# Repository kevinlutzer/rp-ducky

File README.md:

# RP Ducky

A RP2040 based keystroke injector that uses standard [Ducky Script](https://docs.hak5.org/hak5-usb-rubber-ducky/duckyscript-tm-quick-reference). Unlike the original Rubber Ducky from Hak5, this module does not require the scripts to be loaded over an SD card. Instead, you can start the RP Ducky in USB Storage mode to both update the code and the scripts on the device.

## Fabrication

The PCBs are fabricated as a 4 layer board with JLCPCBs JLC04161H-7628A stackup. The bill of materials and the gerber files are available in the [fab](./fab) folder. The USB covering the PCB is designed for can be found on [Alibaba](https://www.alibaba.com/product-detail/Custom-Logo-2-0-3-0_1600456187162.html?spm=a2700.galleryofferlist.p_offer.d_image.72eb3e85w6j8S4&s=p) or on [Amazon](https://www.amazon.ca/RAOYI-Drives-Memory-Storage-Swivel/dp/B07KS1TTCH?ref_=ast_slp_dp&th=1) 

## Usage

To upload the code and scripts to the RP Ducky, you need to put the RP Ducky into USB Storage mode. To do this, hold the button `BOOT` and `RESET` buttons down while plugging the device into a computer. Release the `BOOT` button first and then the `RESET` button. The device will show up as storage device. Copy Adafruit's [Raspberry Pi Pico UF2 Circuit Python file](https://circuitpython.org/board/raspberry_pi_pico/) on to the RP Ducky. You can then copy the contents of [code](./code/) onto the device. To run the test script, copy `sample/payloads/rickroll_macos.txt` to the RP Ducky's root directory and rename it to `payload.txt`

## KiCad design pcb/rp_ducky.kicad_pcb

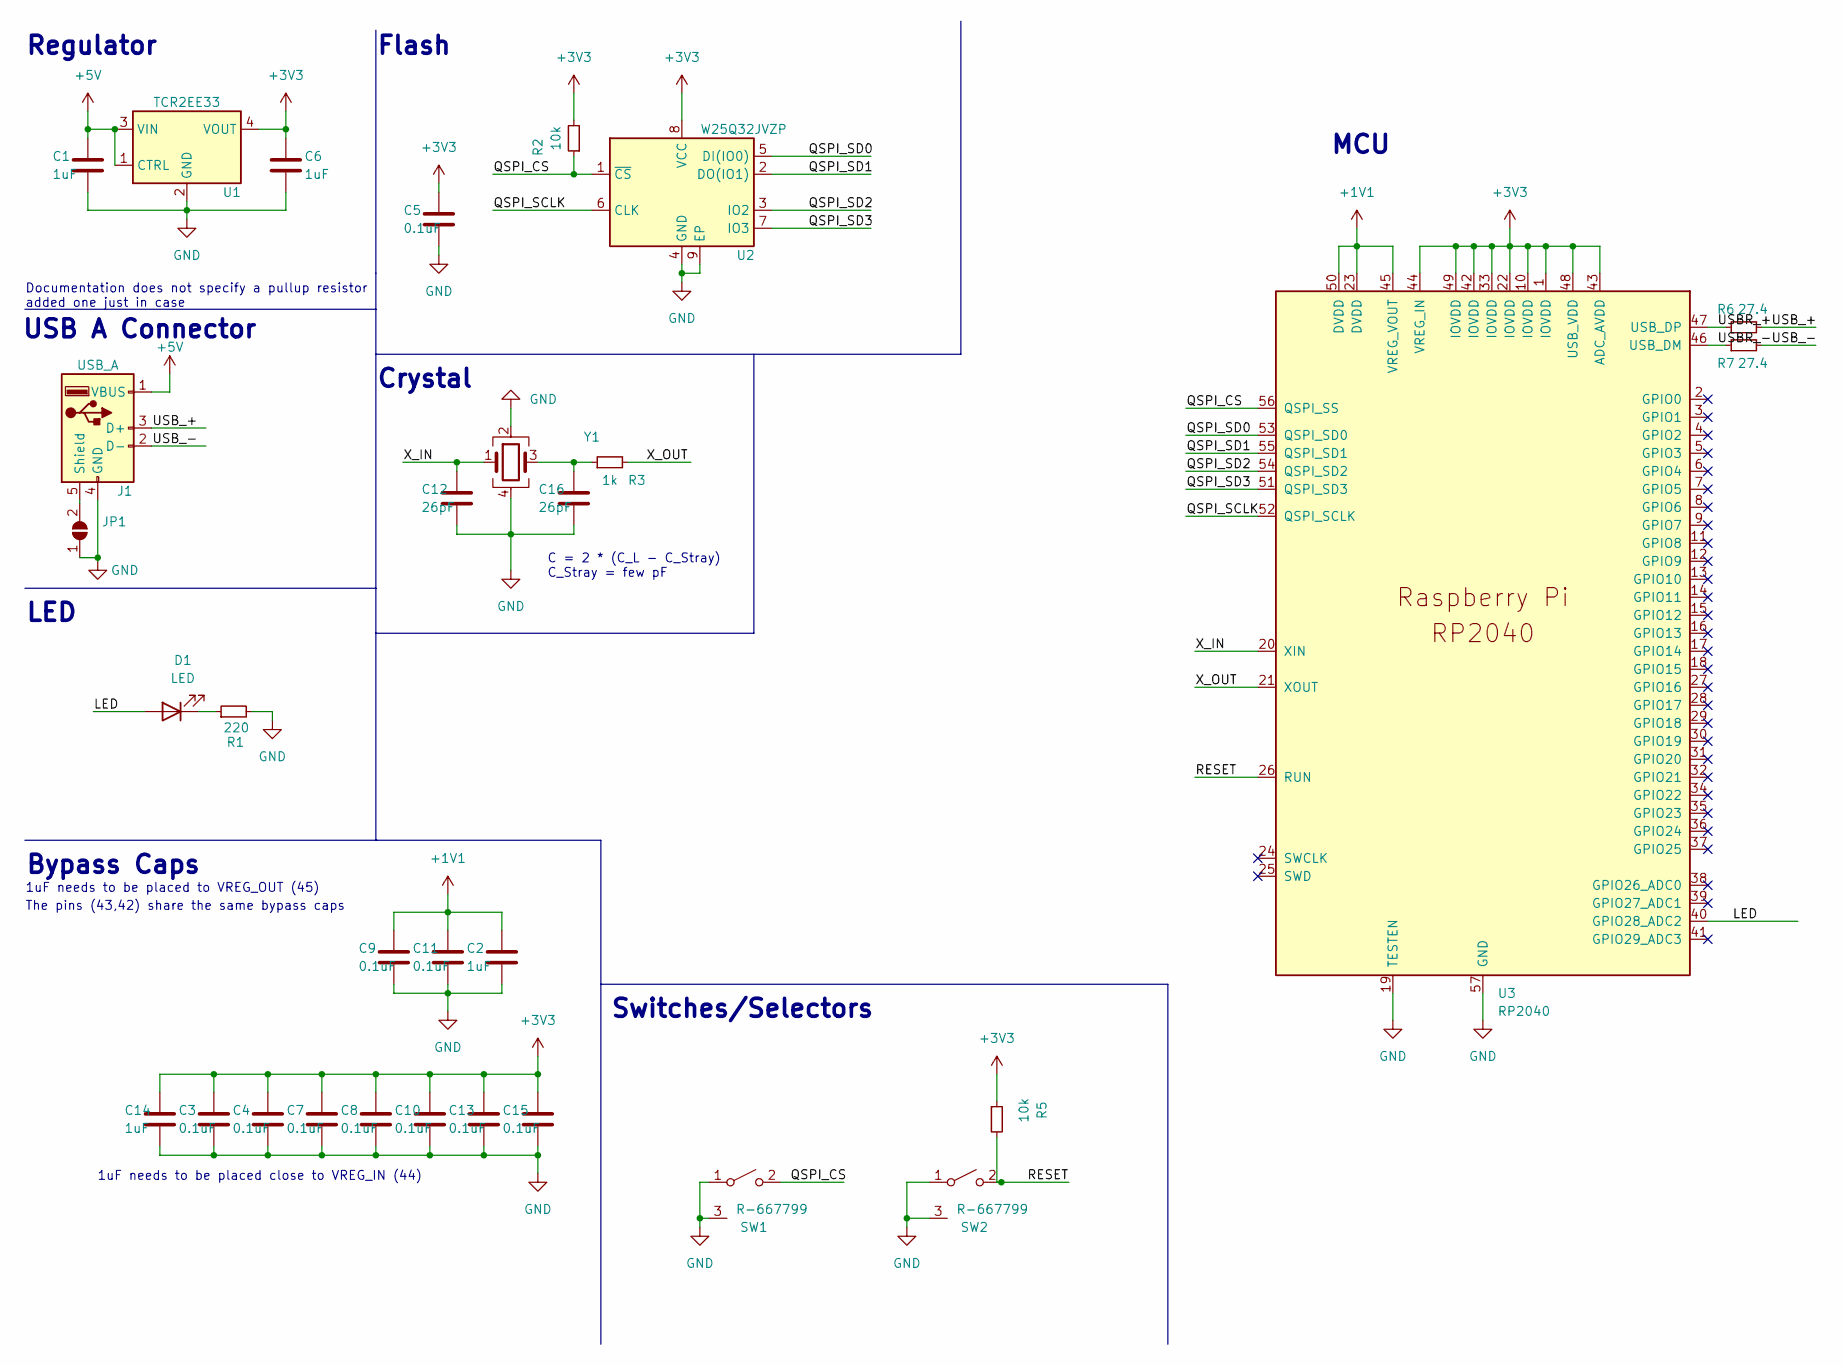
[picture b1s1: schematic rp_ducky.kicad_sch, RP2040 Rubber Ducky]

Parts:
C1, C2, C6: 1uF; C_0402_1005Metric_Pad0.74x0.62mm_HandSolder
C3, C4, C5, C13: 0.1uF; C_0402_1005Metric
C7, C8, C9, C10, C11, C15: 0.1uF; C_0402_1005Metric_Pad0.74x0.62mm_HandSolder
C12, C16: 26pF; C_0402_1005Metric
C14: 1uF; C_0402_1005Metric
D1: LED; LED_0603_1608Metric
J1: USB_A; USB3_A_Plug_Wuerth_629004113921_Horizontal
JP1: SolderJumper_2_Open; SolderJumper-2_P1.3mm_Open_TrianglePad1.0x1.5mm
R1: 220; R_0402_1005Metric
R2, R5: 10k; R_0402_1005Metric
R3: 1k; R_0402_1005Metric
R6, R7: 27.4; R_0402_1005Metric
SW1, SW2: R-667799
U1: TCR2EE33; SOT-553
U2: W25Q32JVZP; WSON-8-1EP_6x5mm_P1.27mm_EP3.4x4.3mm
U3: RP2040; RP2040-QFN-56
Y1: Crystal_GND24; Crystal_SMD_2520-4Pin_2.5x2.0mm

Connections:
+1V1: C2.2, C9.2, C11.2, U3.23 (DVDD), U3.45 (VREG_VOUT), U3.50 (DVDD)
+3V3: C3.2, C4.2, C5.2, C6.2, C7.2, C8.2, C10.2, C13.2, C14.2, C15.2, R2.2, R5.1, U1.4 (VOUT), U2.8 (VCC), U3.1 (IOVDD), U3.10 (IOVDD), U3.22 (IOVDD), U3.33 (IOVDD), U3.42 (IOVDD), U3.43 (ADC_AVDD), U3.44 (VREG_IN), U3.48 (USB_VDD), U3.49 (IOVDD)
+5V: C1.2, J1.1 (VBUS), U1.1 (CTRL), U1.3 (VIN)
/LED: D1.2 (A), U3.40 (GPIO28_ADC2)
/QSPI_CS: R2.1, SW1.2 (B), U2.1 (~CS), U3.56 (QSPI_SS)
/QSPI_SCLK: U2.6 (CLK), U3.52 (QSPI_SCLK)
/QSPI_SD0: U2.5 (DI(IO0)), U3.53 (QSPI_SD0)
/QSPI_SD1: U2.2 (DO(IO1)), U3.55 (QSPI_SD1)
/QSPI_SD2: U2.3 (IO2), U3.54 (QSPI_SD2)
/QSPI_SD3: U2.7 (IO3), U3.51 (QSPI_SD3)
/RESET: R5.2, SW2.2 (B), U3.26 (RUN)
/USBR_+: R6.1, U3.47 (USB_DP)
/USBR_-: R7.1, U3.46 (USB_DM)
/USB_+: J1.3 (D+), R6.2
/USB_-: J1.2 (D-), R7.2
/X_IN: C12.2, U3.20 (XIN), Y1.1
/X_OUT: R3.2, U3.21 (XOUT)
GND: C1.1, C2.1, C3.1, C4.1, C5.1, C6.1, C7.1, C8.1, C9.1, C10.1, C11.1, C12.1, C13.1, C14.1, C15.1, C16.1, J1.4 (GND), JP1.1 (A), R1.2, SW1.1 (A), SW1.3 (SH), SW2.1 (A), SW2.3 (SH), U1.2 (GND), U2.4 (GND), U2.9 (EP), U3.19 (TESTEN), U3.57 (GND), Y1.2, Y1.4
unnamed: C16.2, R3.1, Y1.3
unnamed: D1.1 (K), R1.1
unnamed: J1.5 (Shield), JP1.2 (B)

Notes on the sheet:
Bypass Caps
Switches/Selectors
Crystal
C = 2 * (C_L - C_Stray) C_Stray = few pF
1uF needs to be placed to VREG_OUT (45)
Regulator
1uF needs to be placed close to VREG_IN (44)
Documentation does not specify a pullup resistor added one just in case
The pins (43,42) share the same bypass caps
Flash
USB A Connector
LED
MCU

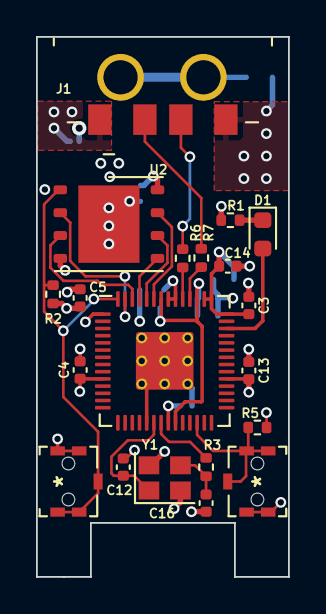
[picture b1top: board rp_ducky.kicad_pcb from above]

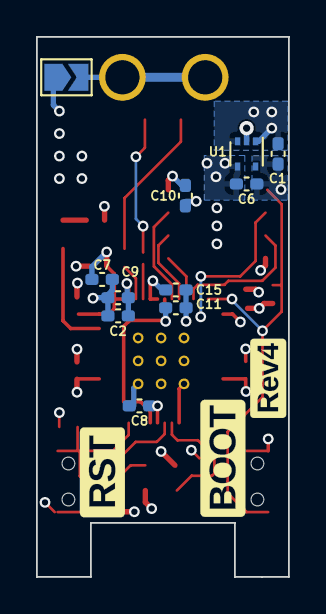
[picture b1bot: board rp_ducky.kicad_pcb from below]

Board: 4 copper layers, 14.0 x 30.0 mm, 31 parts (11 on the bottom side), 21 nets.

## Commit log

2022-04-11 add basic code for the program
2022-04-26 build out most of the schematic, currently working on crystal, what one to use?
2022-04-30 get the placement 90% switch out SW1 and SW2 to buttons that are 1mm thick
2022-05-01 finish most of the inpours, routing and vias
2022-05-02 git ignore
2022-05-03 pass erc
2022-05-03 finish the layout
2022-05-03 add bom
2022-05-04 fix silk screen adnd use 10 pin JTAG programmer
2022-05-04 add backup files
2022-05-04 add pcbs for prints
2022-05-05 add the v1 gerber zips
2022-05-25 add v2
2022-05-25 start stripping v1 features
2022-06-02 route out most of the pcb
2022-06-03 fix issues with mic5504mt compoennt
2022-06-04 finish routing neopizel
2022-06-04 add backups
2022-06-04 remove backup files remove print files remove gerbbers from v2, move v1 fab files to the v1 section
2022-06-04 add the v1 gerbers
2022-06-04 just leave the project behind in the v1 folder
2022-06-04 move pcb files
2022-06-04 move bom file
2022-06-04 add local rp2040, mic5504 symbols and footprints
2022-06-04 remove uneeded files for RP2040 pretty
2022-06-04 update R-667799 kicad footprint
2022-06-05 update the R-667799 footprint and component finish routing
2022-06-06 add silk screen
2022-06-07 pico duck
2022-06-08 more silkscreen cleanup{
2022-06-10 use the weurth usb a connector
2022-06-15 add v2 gerber fab files
2022-07-07 add the v2 bom
2022-09-22 add the v3 files
2022-09-22 move some of the files around deleted the v2 pcb stuff
2022-09-22 fix the rp ducky stuff
2022-09-22 cleanup gitignore
2022-10-08 add some code that works for the prototype
2022-10-19 remove level shifter for the SK8012 rgb led
2022-10-19 add rev4 label and update the pcb to use it
2022-11-02 add v4 gerbers
2022-11-15 update the ibom and gerbers
2023-07-22 use 0402 parts only, on the bottom use larger solderable pads
2023-08-31 add a .lck ignore line to the gitignore
2023-10-11 documentation
